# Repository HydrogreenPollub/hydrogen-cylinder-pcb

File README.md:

## Hydrogen cylinder unit PCB

CADLAB preview: [link](https://cadlab.io/project/27808)

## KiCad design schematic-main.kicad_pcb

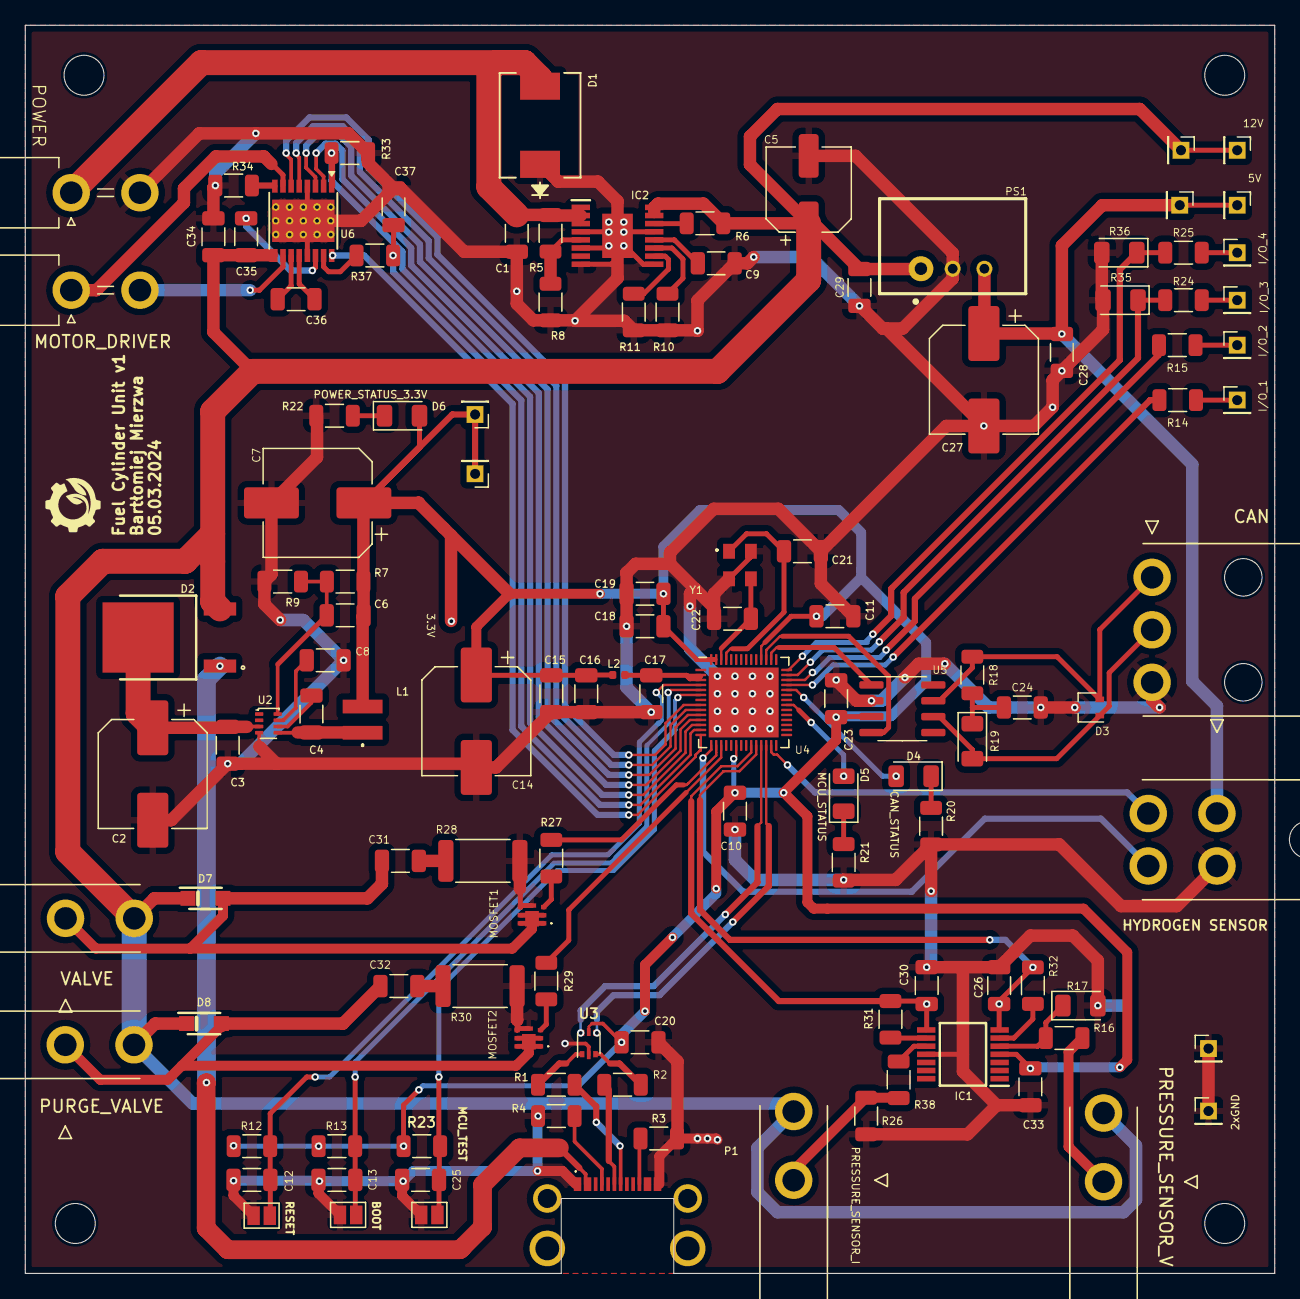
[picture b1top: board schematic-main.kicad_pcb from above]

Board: 2 copper layers, 100.0 x 99.9 mm, 124 parts (0 on the bottom side), 78 nets.

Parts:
C1, C12, C13, C15, C18, C25: 1u; C_1206_3216Metric
C2, C14, C27: 10u; CP_Elec_8x10.5
C3, C4, C10, C11, C16, C17, C20, C23, C28, C29, C33, C34, C35, C36: 100n; C_1206_3216Metric
C5: 47u; CP_Elec_6.3x7.7
C6: 47p; C_1206_3216Metric
C7: 100u; CP_Elec_8x10.5
C8: 33n; C_1206_3216Metric
C9: 2n7; C_1206_3216Metric
C19: 10n; C_1206_3216Metric
C21, C22: 12p; C_1206_3216Metric
C24, C26, C30: 4n7; C_1206_3216Metric
C31, C32: 20n; C_1206_3216Metric
C37: 1n; C_1206_3216Metric
D1: TPSMC30CA; TPSMCSeries_LTF
D2: MBRD20100CT-13; TO252_(DPAK)_1
D3: SP0502BAJT; SOT-323_SC-70
D4, D5, D6: LED; D_1206_3216Metric
D7, D8: PMEG10020; PMEG10020ELR
H1, H2, H3, H4: MountingHole; MountingHole_3.2mm_M3_DIN965
IC1: AD8544ARUZ-REEL; SOP65P640X120-14N
IC2: LM76202QPWPRQ1; SOP65P640X120-17N
J1: Battery; Molex_Mini-Fit_Jr_5569-02A2_2x01_P4.20mm_Horizontal
J2: CAN; 39303035
J3: V_P; 39-30-102Y
J4: Conn_01x04; 39-30-104Y
J7: C_P; 39-30-102Y
J8: VALVE; 39-30-102Y
J9: PURGE_VALVE; 39-30-102Y
J10: Motor; Molex_Mini-Fit_Jr_5569-02A2_2x01_P4.20mm_Horizontal
JP1, JP2, JP3: SolderJumper_2_Open; SolderJumper-2_P1.3mm_Open_Pad1.0x1.5mm
L1: 4u7; SRN3015TA4R7M
L2: 2n; L_0402_1005Metric
MOSFET1, MOSFET2: PMPB15XP_115; PMPB15XPAX
P1: USB_C_Plug_USB2.0; 2169900002
PS1: TSR_1-2450; TSR-1-24120
R1, R2, R38: 0; R_1206_3216Metric
R3, R4: 5k1; R_1206_3216Metric
R5: 180k; R_1206_3216Metric
R6, R11, R37: 100k; R_1206_3216Metric
R7: 32k; R_1206_3216Metric
R8: 12k; R_1206_3216Metric
R9, R12, R13, R23, R33: 10k; R_1206_3216Metric
R10: 56k; R_1206_3216Metric
R14, R15, R20, R21, R22, R31, R32: 1k; R_1206_3216Metric
R16: 5k; R_1206_3216Metric
R17, R35, R36: 10k; LED_1206_3216Metric
R18: 60; R_1206_3216Metric
R19: 60; LED_1206_3216Metric
R24, R25: 100R; R_1206_3216Metric
R26: 150R; R_1206_3216Metric
R27, R29: 180R; R_1206_3216Metric
R28, R30: 100R 0,5W; R_2512_6332Metric
R34: 0.2; R_1206_3216Metric
TP1, TP2: GND; PinHeader_1x01_P2.00mm_Vertical
TP3, TP4: +12V; PinHeader_1x01_P2.00mm_Vertical
TP5, TP6: +5V; PinHeader_1x01_P2.00mm_Vertical
TP7, TP8: +3.3V; PinHeader_1x01_P2.00mm_Vertical
TP9: I/O 1; PinHeader_1x01_P2.00mm_Vertical
TP10: I/O 2; PinHeader_1x01_P2.00mm_Vertical
TP11: I/O 3; PinHeader_1x01_P2.00mm_Vertical
TP12: I/O 4; PinHeader_1x01_P2.00mm_Vertical
U2: TPS62933; SOT-583-8
U3: USBLC6-2P6; SOT-666
U4: ESP32-S3FN8; QFN-56-1EP_7x7mm_P0.4mm_EP5.6x5.6mm
U5: SN65HVD232; SOIC-8_3.9x4.9mm_P1.27mm
U6: DRV8801PWP; HTSSOP-16-1EP_4.4x5mm_P0.65mm_EP3.4x5mm_Mask3x3mm_ThermalVi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
Y1: Crystal_GND24; KC3225K400000C1GE00

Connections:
+3.3V: C6.1, C7.1, C10.1, C11.1, C14.1, C15.1, C16.1, C18.1, C19.1, C20.1, C23.1, C33.1, D6.2 (A), IC1.4 (V+), L1.2, L2.1, R7.1, R12.2, R13.2, R23.2, TP7.1, TP8.1, U3.5 (VBUS), U4.20 (VDD3P3_RTC), U4.46 (VDD3P3_CPU), U4.55 (VDDA), U4.56 (VDDA), U5.3 (VCC)
+5V: C27.1, C28.1, J4.1, PS1.3 (VOUT+), TP5.1, TP6.1
+12V: C5.1, C29.1, C34.1, C35.1, D2.2, D7.1 (K), D8.1 (K), IC2.15 (OUT_1), IC2.16 (OUT_2), J3.2, J7.2, J8.2, J9.2, PS1.1 (VIN+), R6.1, TP3.1, TP4.1, U6.9 (VBB)
/ADC_MOTOR: C37.1, R37.2, U4.13 (GPIO8/ADC1_CH7)
/DECAY_MODE_MOTOR: U4.11 (GPIO6/ADC1_CH5), U6.2 (MODE1)
/DIRECTION_MOTOR: U4.10 (GPIO5/ADC1_CH4), U6.3 (PHASE)
/DRIVER_SIDE: U4.14 (GPIO9/ADC1_CH8), U6.16 (MODE2)
/ENABLE_MOTOR: U4.8 (GPIO3/ADC1_CH2), U6.6 (ENABLE)
/FAULT_MOTOR: R33.1, U4.12 (GPIO7/ADC1_CH6), U6.1 (~FAULT)
/HYDROGEN_SENSOR_: J4.3, U4.27 (GPIO21)
/HYDROGEN_SENSOR_ADC: J4.4, U4.15 (GPIO10/ADC1_CH9)
/IO/CANH: D3.2 (K), J2.1, R18.2, U5.7 (CANH)
/IO/CANL: D3.1 (K), J2.2, R19.2, U5.6 (CANL)
/IO/CAN_RX: U4.44 (MTCK/JTAG/GPIO39), U5.1 (D)
/IO/CAN_TX: U4.45 (MTDO/JTAG/GPIO40), U5.4 (R)
/IO/LED_CAN_STATUS: D4.2 (A), U4.38 (GPIO33)
/IO/LED_MCU_STATUS: D5.2 (A), U4.35 (SPID/GPIO32)
/IO/PRESSURE_SENSOR_I: J7.1, R26.2, R38.1
/IO/PRESSURE_SENSOR_V: J3.1, R16.1
/IO/PURGE_VALVE: C32.1, D8.2 (A), J9.1, MOSFET2.1, MOSFET2.2, MOSFET2.5, MOSFET2.6, MOSFET2.7
/IO/VALVE: C31.1, D7.2 (A), J8.1, MOSFET1.1, MOSFET1.2, MOSFET1.5, MOSFET1.6, MOSFET1.7
/IO_2/+MOTOR: J10.1, U6.7 (OUT+)
/IO_2/-MOTOR: J10.2, U6.10 (OUT-)
/I/O_1_MCU: R14.2, U4.39 (GPIO34)
/I/O_2_MCU: R15.2, U4.40 (GPIO35)
/I/O_3_MCU: R24.2, R35.1, U4.41 (GPIO36)
/I/O_4_MCU: R25.2, R36.1, U4.42 (GPIO37)
/MCU/BOOT: C13.1, JP2.1 (A), R13.1, U4.5 (GPIO0/BOOT)
/MCU/MCU_TEST: C25.1, JP3.1 (A), R23.1, U4.6 (GPIO1/ADC1_CH0)
/MCU/RESET: C12.1, JP1.1 (A), R12.1, U4.4 (CHIP_PU/RESET)
/MCU/USB_D+: R2.2, U3.3 (I/O2), U3.4 (I/O2), U4.26 (GPIO20/USB_D+/ADC2_CH9)
/MCU/USB_D-: R1.2, U3.1 (I/O1), U3.6 (I/O1), U4.25 (GPIO19/USB_D-/ADC2_CH8)
/MCU/XTAL_N: C21.1, U4.53 (XTAL_N), Y1.1
/MCU/XTAL_P: C22.1, U4.54 (XTAL_P), Y1.3
/PRESSURE_SENSOR_I_MCU: C30.1, IC1.8 (OUT_C), R31.1, U4.23 (GPIO17/ADC2_CH6)
/PRESSURE_SENSOR_V_MCU: C26.1, IC1.7 (OUT_B), R32.2, U4.24 (GPIO18/ADC2_CH7)
/PURGE_VALVE_MCU: R29.2, U4.17 (GPIO12/ADC2_CH1)
/Power /Vin: C1.1, D1.2 (A), IC2.1 (IN_1), IC2.2 (IN_2), IC2.3 (UVLO), J1.1, R5.1
/SLEEP_MOTOR: U4.9 (GPIO4/ADC1_CH3), U6.5 (~SLEEP)
/VALVE_MCU: R27.2, U4.16 (GPIO11/ADC2_CH0)
/VBUS: D2.1, P1.A4 (VBUS), P1.A9 (VBUS), P1.B4 (VBUS), P1.B9 (VBUS)
GND: C1.2, C2.2, C3.2, C5.2, C7.2, C8.2, C9.2, C10.2, C11.2, C12.2, C13.2, C14.2, C15.2, C16.2, C17.2, C18.2, C19.2, C20.2, C21.2, C22.2, C23.2, C24.2, C25.2, C26.2, C27.2, C28.2, C29.2, C30.2, C33.2, C34.2, C37.2, D1.1 (K), D3.3 (A), IC1.11 (GND), IC2.4 (NC_1), IC2.6 (MODE), IC2.8 (RTN), IC2.9 (GND), IC2.13 (NC_2), IC2.17 (EP), J1.2, J2.3, J4.2, JP1.2 (B), JP2.2 (B), JP3.2 (B), MOSFET1.4, MOSFET1.8, MOSFET2.4, MOSFET2.8, P1.A1 (GND), P1.A12 (GND), P1.B1 (GND), P1.B12 (GND), PS1.2 (GND), R3.2, R4.2, R8.2, R9.2, R10.2, R11.2, R17.2, R20.2, R21.2, R22.2, R26.1, R28.2, R30.2, R33.2, R34.2, R35.2, R36.2, TP1.1, TP2.1, U2.4 (GND), U3.2 (GND), U4.57 (GND), U5.2 (GND), U6.4 (GND), U6.13 (GND), U6.17 (GND(PPAD)), Y1.2, Y1.4
unnamed: C24.1, R18.1, R19.1
unnamed: C31.2, R28.1
unnamed: C32.2, R30.1
unnamed: D4.1 (K), R20.1
unnamed: D5.1 (K), R21.1
unnamed: D6.1 (K), R22.1
unnamed: IC1.5 (+IN_B), R16.2, R17.1
unnamed: IC1.10 (+IN_C), R38.2
unnamed: IC1.6 (-IN_B), R32.1
unnamed: IC1.9 (-IN_C), R31.2
unnamed: C9.1, IC2.12 (DVDT)
unnamed: IC2.11 (ILIM), R10.1
unnamed: IC2.10 (IMON), R11.1
unnamed: IC2.5 (OVP), R5.2, R8.1
unnamed: IC2.14 (~FLT), R6.2
unnamed: MOSFET1.3, R27.1
unnamed: MOSFET2.3, R29.1
unnamed: P1.A5 (CC), R4.1
unnamed: P1.A6 (D+), R2.1
unnamed: P1.A7 (D-), R1.1
unnamed: P1.B5 (VCONN), R3.1
unnamed: R14.1, TP9.1
unnamed: R15.1, TP10.1
unnamed: R24.1, TP11.1
unnamed: R25.1, TP12.1
unnamed: C4.1, U2.6 (BST)
unnamed: C6.2, R7.2, R9.1, U2.8 (FB)
unnamed: C8.1, U2.7 (SS)
unnamed: C4.2, L1.1, U2.5 (SW)
unnamed: C2.1, C3.1, D2.3, U2.3 (VIN)
unnamed: C36.1, U6.11 (CP1)
unnamed: C36.2, U6.12 (CP2)
unnamed: R34.1, U6.8 (SENSE)
unnamed: C35.2, U6.14 (VCP)
unnamed: R37.1, U6.15 (VPROPI)
VDD3P3: C17.1, L2.2, U4.2 (VDD3P3), U4.3 (VDD3P3)

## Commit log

2023-10-17 Send initial files
2024-02-10 Repair & add IO schema
2024-02-23 Add footprints
2024-02-23 Add footprints, Placing MCU
2024-02-26 Backlink to CADLAB.io has been added.
2024-02-26 Update README.md with CADLAB link
2024-03-05 Drawing PCB
2024-03-05 Makin GND sphere
2024-03-07 Changing resistance of Voltage divider
2024-03-12 Adding connector for Hydrogen Sensor
2024-03-17 Adding motor driver unit
2024-03-19 Change of dimensions
2024-03-22 Change of PRESSURE_SENSOR_I circuit
2024-03-22 Change of signatures
2024-03-26 Change of socket for Hudrogen sensor
2024-03-26 Silkscreen
2024-03-27 Changing width of mounting holes
2024-03-28 Change presure sensor socket
2024-03-28 Adding descriptions
2024-03-28 Adding descriptions V2
2024-03-30 DRC test copmlate
2024-03-30 PCB complate
2024-04-05 Rename and send to production
